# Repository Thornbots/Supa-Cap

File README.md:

Rose-Hulman's Thornbot's Electrical Team's Super Capacitor Bank

This is an active, work in progress super capacitor bank and super capacitor controller board design that is intended to be used with the DJI Robomaster's competetion. 

User Guide (Currently non-existent, but will be completed eventually) can be found in Documentation
PCB Files can be found in the Design Files folder, with all of the projects being done in KiCAD 8.0. 

Use this design at your own risk, as nothing is guranteed to work and/or be safe.
Enjoy, and ask any questions in our [Team's Discord](https://discord.gg/jRsZXSR5GN). :)

The Software Repository for this hardware can be found at: https://github.com/Thornbots/SupaCap_Software

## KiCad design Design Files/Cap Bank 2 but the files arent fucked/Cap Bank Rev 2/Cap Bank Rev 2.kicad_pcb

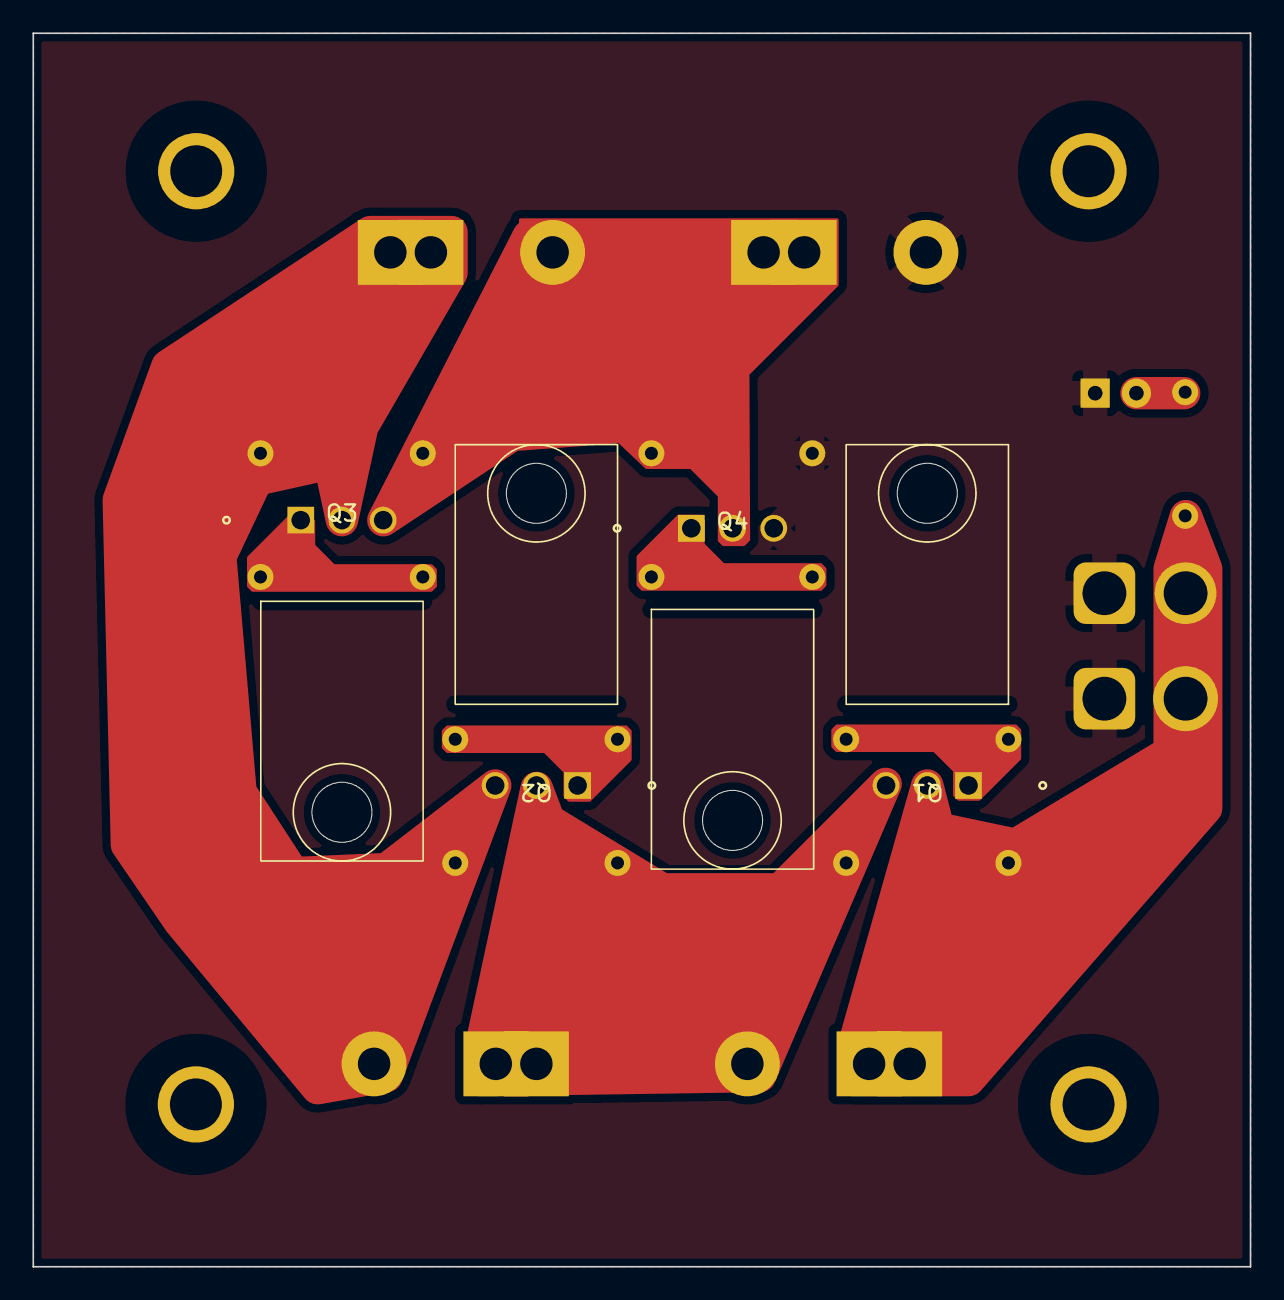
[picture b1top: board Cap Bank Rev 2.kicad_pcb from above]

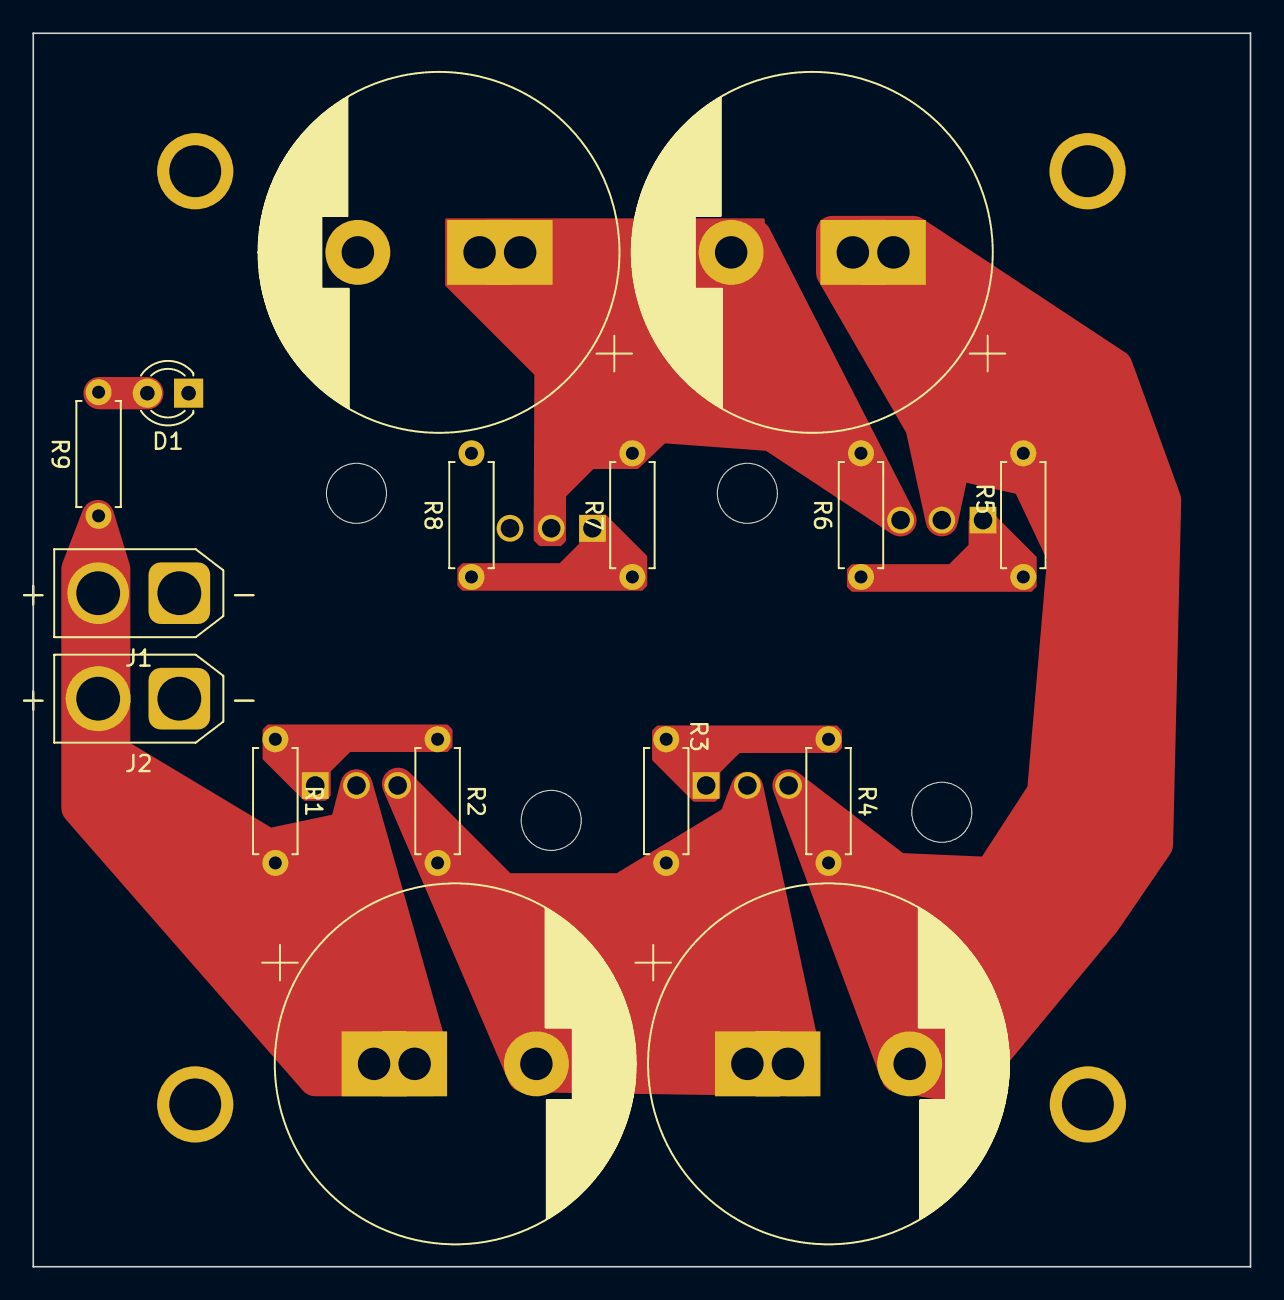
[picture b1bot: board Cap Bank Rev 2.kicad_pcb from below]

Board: 2 copper layers, 75.0 x 76.0 mm, 20 parts (16 on the bottom side), 10 nets.

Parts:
C1, C3, C5, C7: C_Polarized; bigcap
D1: LED; LED_D3.0mm_Clear
J1: Conn_01x02; AMASS_XT30U-M_1x02_P5.0mm_Vertical
J2: Conn_01x02; AMASS_XT30U-F_1x02_P5.0mm_Vertical
Q1, Q2, Q3, Q4: TIP31; tip31sideways
R1, R3, R5, R7: R_Axial_DIN0207_L6.3mm_D2.5mm_P7.62mm_Horizontal
R2, R4, R6, R8: 20k; R_Axial_DIN0207_L6.3mm_D2.5mm_P7.62mm_Horizontal
R9: 1740; R_Axial_DIN0207_L6.3mm_D2.5mm_P7.62mm_Horizontal

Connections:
/GND: C7.2, D1.1 (K), J1.1, J2.1, Q4.3 (E), R8.2
/V_IN: C1.1, J1.2, J2.2, Q1.2 (C), R1.2, R9.1
unnamed: D1.2 (A), R9.2
unnamed: Q1.1 (B), R1.1, R2.1
unnamed: C1.2, C3.1, Q1.3 (E), Q2.2 (C), R2.2, R3.2
unnamed: Q2.1 (B), R3.1, R4.1
unnamed: C3.2, C5.1, Q2.3 (E), Q3.2 (C), R4.2, R5.2
unnamed: Q3.1 (B), R5.1, R6.1
unnamed: C5.2, C7.1, Q3.3 (E), Q4.2 (C), R6.2, R7.2
unnamed: Q4.1 (B), R7.1, R8.1

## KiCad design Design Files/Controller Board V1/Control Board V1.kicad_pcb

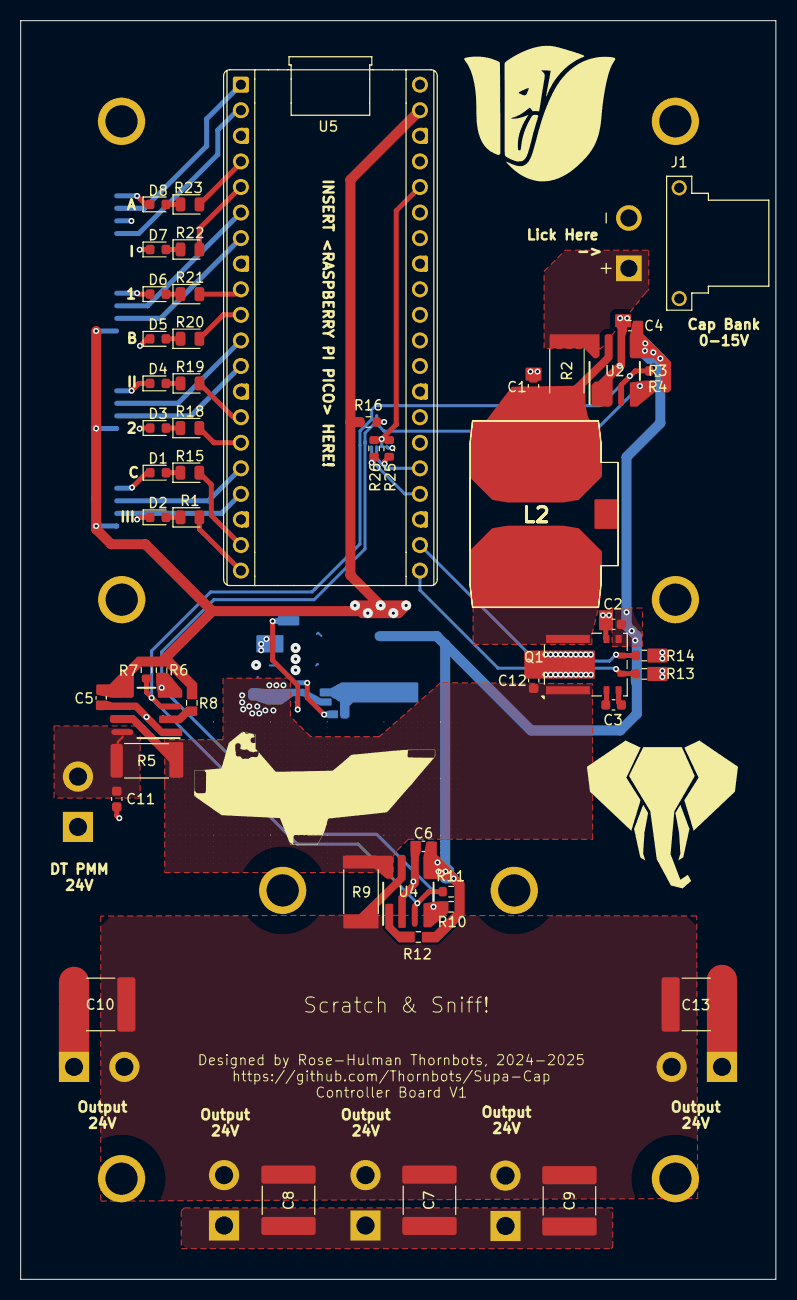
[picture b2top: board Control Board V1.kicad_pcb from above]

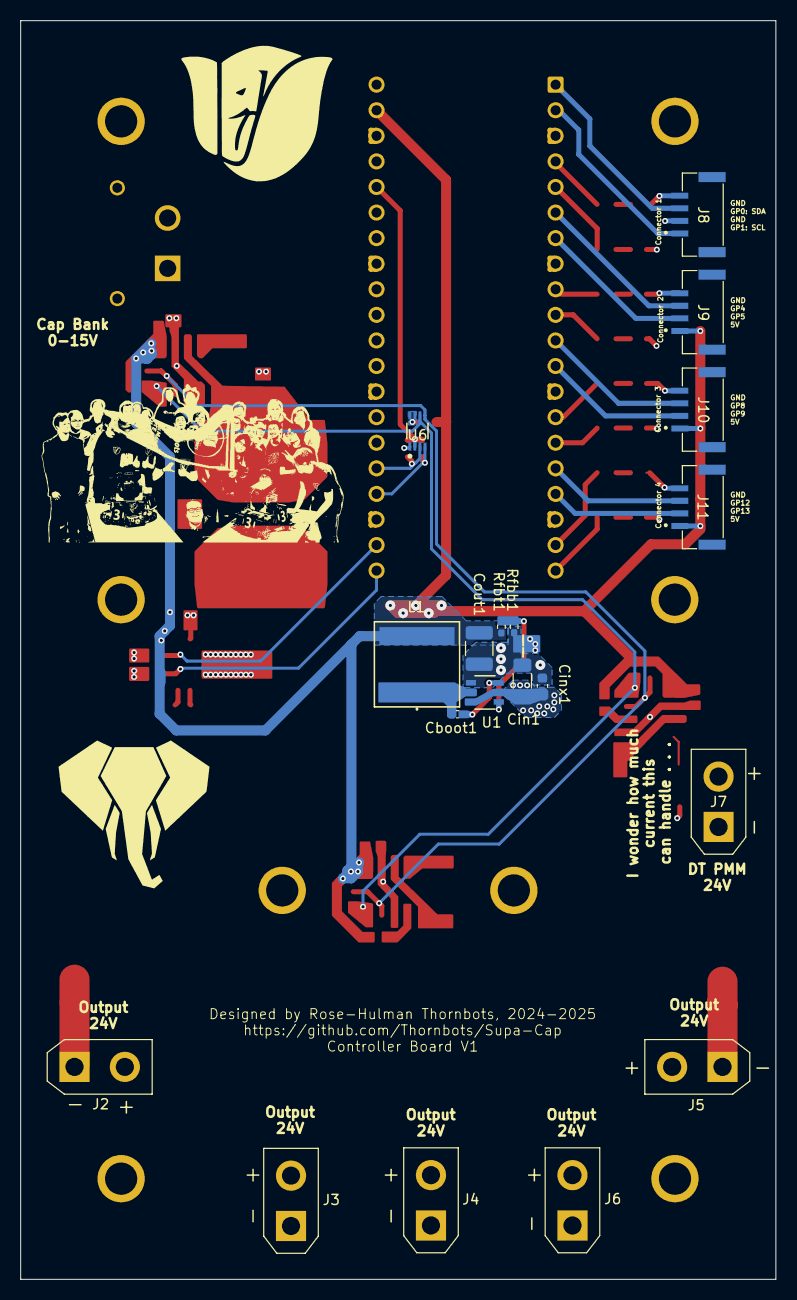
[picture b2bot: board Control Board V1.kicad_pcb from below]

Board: 4 copper layers, 75.0 x 125.0 mm, 70 parts (19 on the bottom side), 47 nets.

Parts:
C1, C11, C12: 10u; C_0603_1608Metric
C2, C3: 0.1u; C_0603_1608Metric
C4, C5, C6: 100 nF; C_0603_1608Metric
C7, C8, C9, C10, C13: 47u; C_2220_5750Metric
Cboot1: 100 nF; C_0402_1005Metric_Pad0.74x0.62mm_HandSolder
Cin1: 2.2 uF; C_1206_3216Metric_Pad1.33x1.80mm_HandSolder
Cinx1: 100 nF; C_0603_1608Metric
Cout1: 47 uF; C_1210_3225Metric_Pad1.33x2.70mm_HandSolder
D1, D2, D3, D4, D5, D6, D7, D8: LED; LED_0603_1608Metric
J1: XT30PW-F
J2, J3, J4, J5, J6, J7: XT30UPB-M; AMASS_XT30UPB-M_1x02_P5.0mm_Vertical
J8, J9, J10, J11: SM04B-GHS-TB_LF__SN_-; JST_SM04B-GHS-TB_LF__SN_-
L1: 10 uH; IND_TAIYO_NRS8030_TAY
Q1: LMG5200; Texas_MOF0009A
R1, R15, R18, R19, R20, R21, R22: R; LED_0805_2012Metric
R2, R5, R9: 0.01Ω; R_2512_6332Metric
R3, R4, R6, R7, R8, R10, R11, R12: 10KΩ; R_0603_1608Metric
R13, R14: 2k; R_0603_1608Metric
R16: 200k; R_0603_1608Metric
R23: 110; LED_0805_2012Metric
R25, R26: 10k; R_0603_1608Metric
Rfbb1: 22.1 kOhm; R_0402_1005Metric_Pad0.72x0.64mm_HandSolder
Rfbt1: 162 kOhm; R_0402_1005Metric_Pad0.72x0.64mm_HandSolder
U1: LMR51420XDDCR; SOT23_DDC_TEX
U2, U3, U4: INA219BIDR; INA219
U5: SC0917; RaspberryPi_Pico_Common_THT
U6: TCA39306DCUR; DCU0008A-MFG

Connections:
3.3V: R25.1, R26.1, U5.36 (3V3_OUT), U6.2 (VREF1)
5V: C2.1, C4.1, C5.1, C6.1, Cout1.1, J9.1, J10.1, J11.1, L1.2, Q1.6 (VCC), R3.1, R4.1, R6.1, R7.1, R8.1, R10.1, R11.1, R12.1, R16.1, Rfbt1.1, U2.5 (VS), U3.5 (VS), U4.5 (VS), U5.39 (VSYS)
/24V_IN: C12.2, Cin1.1, Cinx1.1, Q1.1, R5.2, R9.1, U1.3 (VIN), U1.5 (EN), U3.7 (VIN-), U4.8 (VIN+)
/24V_OUT: C7.2, C8.2, C9.2, C10.2, C13.2, J2.P, J3.P, J4.P, J5.P, J6.P, R9.2, U4.7 (VIN-)
/24_IN_PMM: C11.2, J7.P, R5.1, U3.8 (VIN+)
/CAP_IN: J1.P, R2.1, U2.8 (VIN+)
/I2C_current_SCL: R3.2, R6.2, R10.2, U2.4 (SCL), U3.4 (SCL), U4.4 (SCL), U6.6 (SCL2)
/I2C_current_SDA: R4.2, R7.2, R11.2, U2.3 (SDA), U3.3 (SDA), U4.3 (SDA), U6.5 (SDA2)
/IO/GPIO_0: J11.2, U5.17 (GP13)
/IO/GPIO_1: J11.3, U5.16 (GP12)
/IO/GPIO_2: J10.2, U5.12 (GP9)
/IO/GPIO_3: J10.3, U5.11 (GP8)
/IO/GPIO_4: J9.2, U5.7 (GP5)
/IO/GPIO_5: J9.3, U5.6 (GP4)
/IO/I2C_TypeC_SCL: J8.1, U5.2 (GP1)
/IO/I2C_TypeC_SDA: J8.3, U5.1 (GP0)
/PWM_bottom: Q1.5 (LI), R13.1, U5.22 (GP17)
/PWM_top: Q1.4 (HI), R14.1, U5.21 (GP16)
/Pico/LED0: R1.2, U5.20 (GP15)
/Pico/LED1: R15.2, U5.19 (GP14)
/Pico/LED2: R18.2, U5.15 (GP11)
/Pico/LED3: R19.2, U5.14 (GP10)
/Pico/LED4: R20.2, U5.10 (GP7)
/Pico/LED5: R21.2, U5.9 (GP6)
/Pico/LED6: R22.2, U5.5 (GP3)
/Pico/LED7: R23.2, U5.4 (GP2)
/cap_volt: C1.2, R2.2, U2.7 (VIN-)
D_GND: C4.2, C5.2, C6.2, D1.1 (K), D2.1 (K), D3.1 (K), D4.1 (K), D5.1 (K), D6.1 (K), D7.1 (K), D8.1 (K), J8.2, J8.4, J9.4, J10.4, J11.4, R13.2, R14.2, U2.1 (A1), U2.2 (A0), U2.6 (GND), U3.1 (A1), U3.6 (GND), U4.2 (A0), U4.6 (GND), U5.3 (GND), U5.8 (GND__1), U5.13 (GND__2), U5.18 (GND__3), U5.23 (GND__4), U5.28 (GND__5), U5.33 (AGND), U5.38 (GND__6), U6.1 (GND)
unnamed: D1.2 (A), R15.1
unnamed: D2.2 (A), R1.1
unnamed: D3.2 (A), R18.1
unnamed: D4.2 (A), R19.1
unnamed: D5.2 (A), R20.1
unnamed: D6.2 (A), R21.1
unnamed: D7.2 (A), R22.1
unnamed: D8.2 (A), R23.1
unnamed: C3.1, Q1.2 (HB)
unnamed: C3.2, Q1.3 (HS)
unnamed: Cboot1.1, U1.6 (CB)
unnamed: Rfbb1.1, Rfbt1.2, U1.4 (FB)
unnamed: Cboot1.2, L1.1, U1.2 (SW)
unnamed: R8.2, U3.2 (A0)
unnamed: R12.2, U4.1 (A1)
unnamed: R26.2, U5.24 (GP18), U6.4 (SDA1)
unnamed: R25.2, U5.25 (GP19), U6.3 (SCL1)
unnamed: R16.2, U6.7 (VREF2), U6.8 (EN)
P_GND: C1.1, C2.2, C7.1, C8.1, C9.1, C10.1, C11.1, C12.1, C13.1, Cin1.2, Cinx1.2, Cout1.2, J1.N, J2.N, J3.N, J4.N, J5.N, J6.N, J7.N, Q1.7 (AGND), Q1.9, Rfbb1.2, U1.1 (GND)

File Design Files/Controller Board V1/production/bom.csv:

Designator,Footprint,Quantity,Value,LCSC Part #
"C1, C11, C12",0603,3,10u,
"C10, C13, C7, C8, C9",2220,5,47u,
"C2, C3",0603,2,0.1u,
"C4, C5, C6, CINX1",0603,4,100 nF,
CBOOT1,0402,1,100 nF,
CIN1,1206,1,2.2 uF,
COUT1,1210,1,47 uF,
"D1, D2, D3, D4, D5, D6, D7, D8",0603,8,LED,
J1,XT30PW-F,1,XT30PW-F,
"J10, J11, J8, J9",JST_SM04B-GHS-TB_LF__SN_-,4,SM04B-GHS-TB_LF__SN_-,
"J2, J3, J4, J5, J6, J7",AMASS_XT30UPB-M_1x02_P5.0mm_Vertical,6,XT30UPB-M,
L1,IND_TAIYO_NRS8030_TAY,1,10 uH,
Q1,Texas_MOF0009A,1,LMG5200,
"R1, R15, R18, R19, R20, R21, R22",0805,7,R,
"R10, R11, R12, R3, R4, R6, R7, R8",0603,8,10KΩ,
"R13, R14",0603,2,2k,
R16,0603,1,200k,
"R2, R5, R9",2512,3,0.01Ω,
R23,0805,1,110,
"R25, R26",0603,2,10k,
RFBB1,0402,1,22.1 kOhm,
RFBT1,0402,1,162 kOhm,
U1,SOT23_DDC_TEX,1,LMR51420XDDCR,
"U2, U3, U4",INA219,3,INA219BIDR,
U5,RaspberryPi_Pico_Common_THT,1,SC0917,
U6,DCU0008A-MFG,1,TCA39306DCUR,

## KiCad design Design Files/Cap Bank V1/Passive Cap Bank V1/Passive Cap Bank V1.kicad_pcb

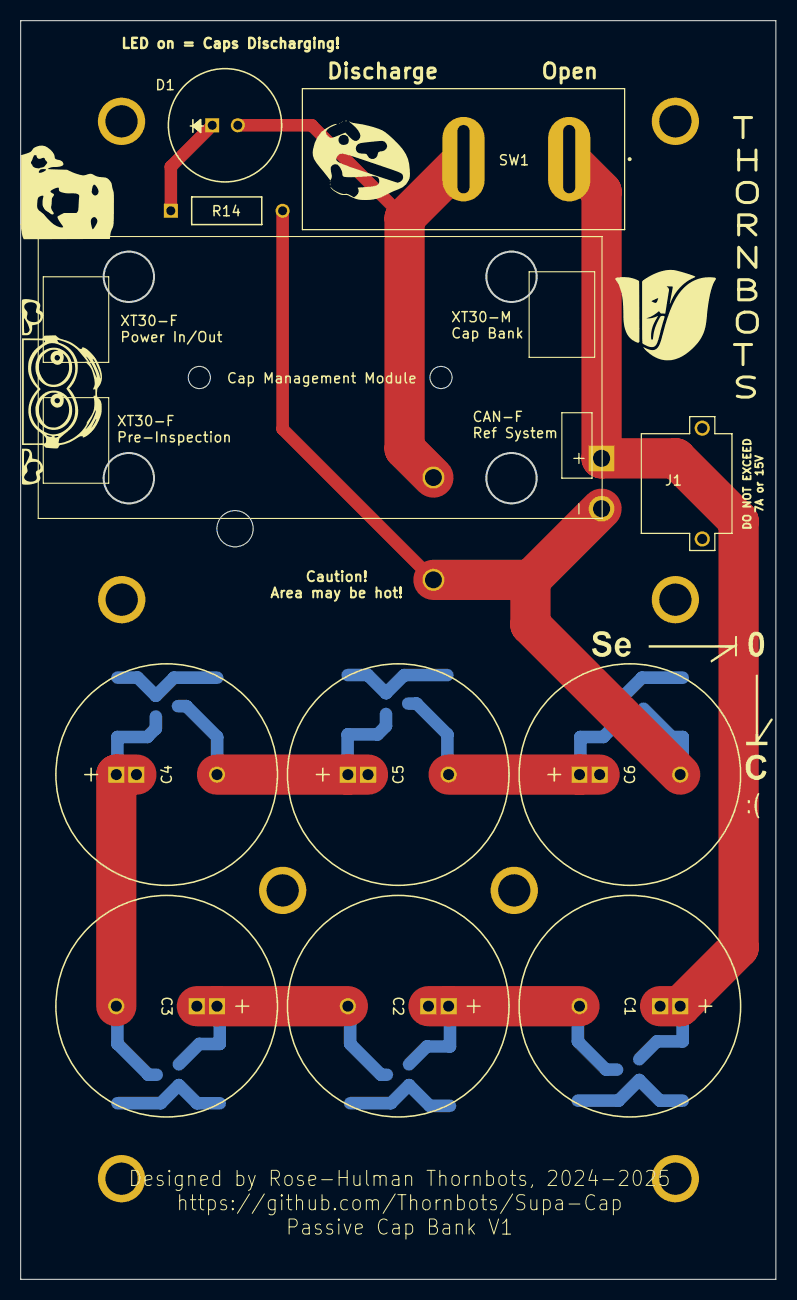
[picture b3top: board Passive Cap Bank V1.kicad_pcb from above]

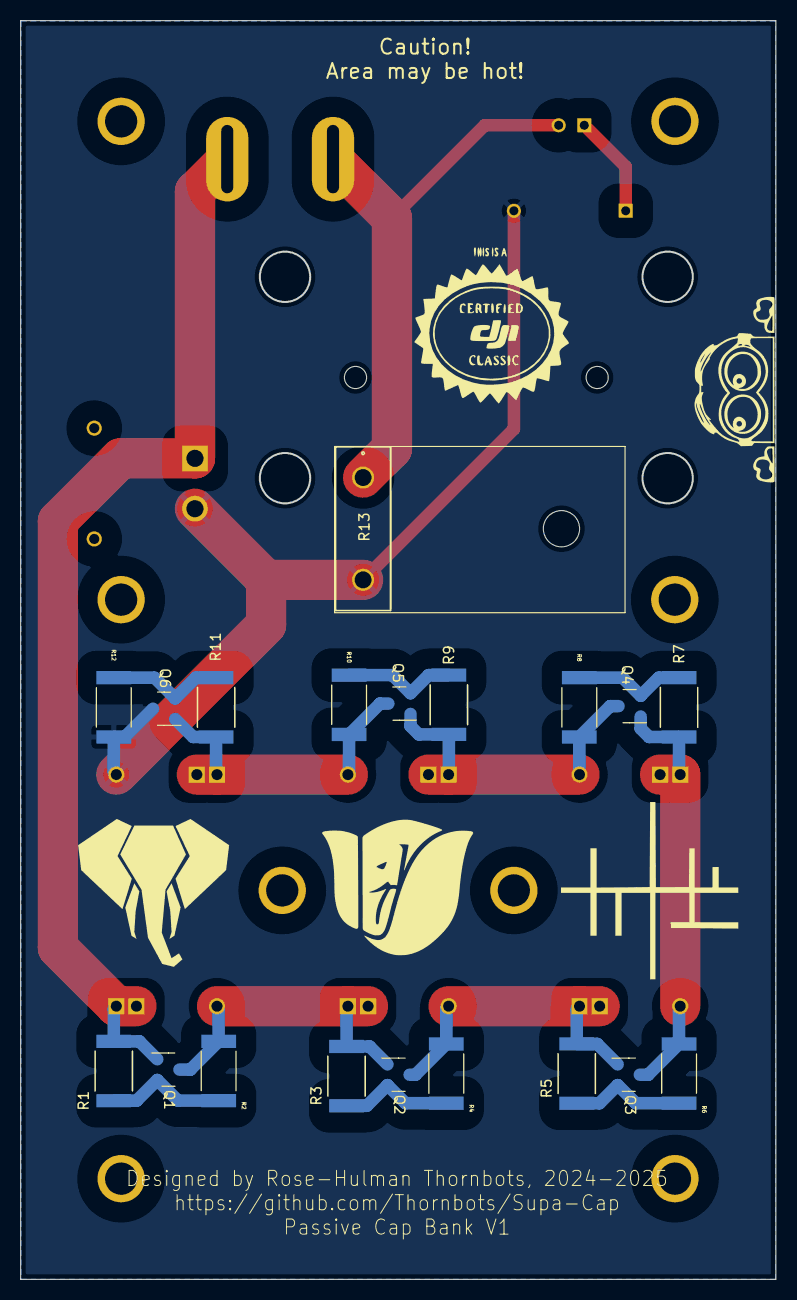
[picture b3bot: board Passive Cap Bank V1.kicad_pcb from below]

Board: 2 copper layers, 75.0 x 125.0 mm, 29 parts (19 on the bottom side), 15 nets.

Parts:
C1, C2, C3, C4, C5, C6: 100F; 100F Kyocera Cap
D1: 10mm_LED; 10mm LED
J1: XT30-Male; XT30PW-M
Q1, Q2, Q3, Q4, Q5, Q6: BC817-40; NPN BJT
R1, R3, R5, R7, R9, R11: 20k; 20kResistor
R2, R4, R6, R8, R10, R12: 7.87k; 787Resistor
R13: 2 : 100Watt; 100Watt2
R14: 680; 680 Resistor
SW1: SW_Push_Open; SW_RB141C1100

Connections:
GND: C6.2 (-), J1.N, Q6.3 (E), R12.2, R13.3, R14.2
unnamed: C1.2 (-), C2.1 (+), Q1.3 (E), Q2.1 (C), R2.2, R3.1
unnamed: C2.2 (-), C3.1 (+), Q2.3 (E), Q3.1 (C), R4.2, R5.1
unnamed: C3.2 (-), C4.1 (+), Q3.3 (E), Q4.1 (C), R6.2, R7.1
unnamed: C4.2 (-), C5.1 (+), Q4.3 (E), Q5.1 (C), R8.2, R9.1
unnamed: C5.2 (-), C6.1 (+), Q5.3 (E), Q6.1 (C), R10.2, R11.1
unnamed: D1.2 (A), R13.1, SW1.2 (B)
unnamed: D1.1 (K), R14.1
unnamed: Q1.2 (B), R1.2, R2.1
unnamed: Q2.2 (B), R3.2, R4.1
unnamed: Q3.2 (B), R5.2, R6.1
unnamed: Q4.2 (B), R7.2, R8.1
unnamed: Q5.2 (B), R9.2, R10.1
unnamed: Q6.2 (B), R11.2, R12.1
V_15: C1.1 (+), J1.P, Q1.1 (C), R1.1, SW1.1 (A)

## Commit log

2024-07-20 Initial Push
2024-07-24 Adding data sheets for parts that will probably work
2024-10-23 Adding Simulations Folder
2024-10-24 Cap Bank V1 Schematic Done. Layout started
2024-10-24 Started Layout
2024-10-25 Layout and Routing Progress
2024-10-25 Routing done. Luci is amazing
2024-10-27 Minor Changes. Added Logo and warnings
2024-10-27 I have a fork now
2024-10-28 Board is now shorter
    womp womp
2024-10-28 Started Control Board, added LDO
2024-10-29 Added to Control Board Schematic
2024-11-03 supercap boad layout back maybe change
    title
2024-11-04 I don't understand
2024-11-10 Extended copper pad on back
    copper!!!! so cool!!
2024-11-10 Added TI DC DC IC
2024-11-10 Added LM chip for 5V supply
2024-11-10 Power Supply Board For Pico
2024-12-15 redid placements and routing
2024-12-16 Almost done, just need silkscreen finalized
2024-12-17 mech changes
2024-12-17 mech finalized
2025-01-08 final
2025-01-14 Nothing important
2025-01-14 Added 100 nF capacitor footprint to folder
2025-01-14 Added all the capacitor footprints into the folder
2025-01-15 Changing to the new capacitor footprints. Redoing layout.
2025-01-15 Improved Layout and started routing
2025-01-15 Added missing files
2025-01-15 Routing done, holes and copper pour todo
2025-01-21 Changed to larger board size, layout wip
2025-01-23 Finished layout and routing. Some Silkscreen to do
2025-01-23 Copper Pour done. Silkscreen TODO
2025-01-23 Silkscreen done. Should be complete. Maybe add more silkscreen if wanted
2025-01-26 minor silkscreen changes
2025-01-26 ben changes
2025-01-26 Made the THING
2025-01-27 Added footprint for other cap, also fixed holes not being electically isolated
2025-01-27 Cleaned up Repo and added Gerber files
2025-01-28 cap holes fixed
2025-02-02 final cap bank changes
2025-02-02 Imported XT30-M
2025-02-02 Added male XT30s
2025-02-02 Added the female XT30
2025-02-02 Added jst 4 pin connector
2025-02-03 gerber files
2025-02-04 fixed gerber and pour
2025-02-04 LMG5200 sheet i think
2025-02-04 5v supply pcb
    YIPPEEEE pt2
2025-02-04 small tweaks to half bridge schematic
2025-02-04 Edited XT30 symbols to include solder points
2025-02-06 Added PCB outline, mounting holes, and added design comments
2025-02-06 added pico hierachical thing
    might have messed up some pin names, pico schematic is not yet real, but we got the pins!!
2025-02-06 Rough Layout started
2025-02-09 3x current sensor schematic blocks
    wahoo
2025-02-11 Removed unnecessary files. Created a .gitignore
2025-02-11 Better .gitignore file
2025-02-11 Cleaning the Repo
2025-02-11 resistor footprints
    yuh
2025-02-11 Ignoring zips in Footprints folder
2025-02-11 Spelling is hard
2025-02-11 Pico Schematic Started
2025-02-12 I2C channels for pico and current sensors
    gaming B)
2025-02-13 Assigning footprints and ading to schematic
2025-02-15 Updated pins on PICO schematic
2025-02-16 yay(meeting 2/16/2025)
2025-02-18 Major Schematic Progress
2025-02-18 idk
    drew a instead of getting the footprint
    and tested potential layouts but idk yet
2025-02-18 here we go agane
    Updating footprints and tackling general layout
2025-02-18 the board
    yayyyyyyyyy
2025-02-18 current sensor done
2025-02-18 Added Cap footprint, added LED, added Resistors
2025-02-20 general layout revised
    goodnight
2025-02-20 Changed to four layer and added pours
2025-02-20 Minor Changes
2025-02-20 board
2025-03-03 OOps, pushing late
2025-03-04 traces for current sensor
    yeah
2025-03-04 fancier current sensor traces
    yayyyyyy
2025-03-07 vias updated
2025-03-07 small issues fixed
2025-03-08 some stuff
2025-03-08 finished the stuffs
    yippee
2025-03-09 tweaked 5v to q1
2025-03-10 Added i2c level shifter
2025-03-11 tweaks
2025-03-11 cleaning up stuffs
    5vpsu and pour to cabbage
2025-03-13 tweaked 24v big pour
2025-03-15 half finished with brooks changes
2025-03-15 brooks changes in
2025-03-15 i2c stepdown
    cookies tmrw
2025-03-16 Ready For Design Review
2025-03-16 trace tweak
2025-03-16 Last second changes
2025-03-17 Silkscreen
2025-03-17 Additional silkscreen
2025-03-17 Added hyperlink and kicad version
2025-03-17 Changed to through vias
2025-04-22 Cap Bank V2
    wohoo
2025-04-27 New Cap Bank
    wohooo
2025-04-29 updated again!!!
    ship it!
2025-05-04 new bjt
    who dis
2025-05-06 NO HEATSINKS
    they were too large...
